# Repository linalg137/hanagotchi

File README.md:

# HANAGOTCHI

A small "tamagotchi", shaped like a flower. It has three interactive buttons and an OLED screen, and can play many different files-- coded in micropython. This isn't a generic "pet" tamagotchi-- you're guarding a dangerous invisible criminal-- try not to let them get out!!  

## ***Inspiration***
As a constant fiction writer, I've always wanted to create my own special dialogue-based game. This gave me the perfect chance to do so, while including extrenally aeshtetic pleasures as well.

## ***Full Instructions~***

**getting the pcb**
1. go to https://jlcpcb.com/. click "get instant quote".
2. download the gerber zip file from the pcb folder and upload it.
3. you can change the color of the PCB if you'd like, but keep all the other settings the same.
4. order your PCB by following the steps on the website.

**getting the parts**
1. To find all the suitable parts needed for this pcb, open the BOM file. This lists all the necessary parts needed for the PCB-- you'll see several links leading to product pages.

**printing the case**
1. download the STL files, or go open this onshape link: [https://cad.onshape.com/documents/30ca1b2b31257d2650154877/w/6a6ce5b2935f39e9888c6e90/e/9cf32ad964649424d66e1c2f?renderMode=0&uiState=6a1fb2345d12723005a9a689](https://cad.onshape.com/documents/cbb68b9589daf277c9578781/w/eef88f9737002ddb59d7612d/e/e6992a34dc4435c059d9da9e?renderMode=0&uiState=6a20adc240c23c91ee920c5a).
2. follow the directions on your own 3D printer's manufacturer's website/app to upload the STL files in and print them. support for the prints are not neeeded, as long as you have the models sitting on the correct side.

**soldering and putting everything together**
1. solder the pieces together in their designated spots. You can use the .step file to see how it should look like in the end (the battery cell is optional). 
2. After you're done soldering it, plug the ESP32 into your device using a USB-C.
3. Import micropython onto your ESP32 by uploading the ESP32_GENERIC_C3-20260406-v1.28.0.bin into the adafruit webserial bootloader (https://adafruit.github.io/Adafruit_WebSerial_ESPTool/)(to start this, click the "connect" button on the upper right corner. no offset is needed.).
4. upload the programs into the ESP32 using your coding development environment (ex; Thonny.) whenever you plug in the device, it should immeadiately start playing the intro (main) file!!

## ***GALLERY***
<details>
  <summary>3D model, PCB design, schematic, etc</summary>

</details>

## ***Credits~***
This project used:
- [KiCAD](https://www.kicad.org/) (for PCB design)
- [Onshape](https://www.onshape.com/en/platform) (for case design)
- [@TaniWanKenobi's Tamagotchi Guided Tutorial](https://fallout.hackclub.com/docs/guided-projects/tamagotchi) (for the base schematic layout)

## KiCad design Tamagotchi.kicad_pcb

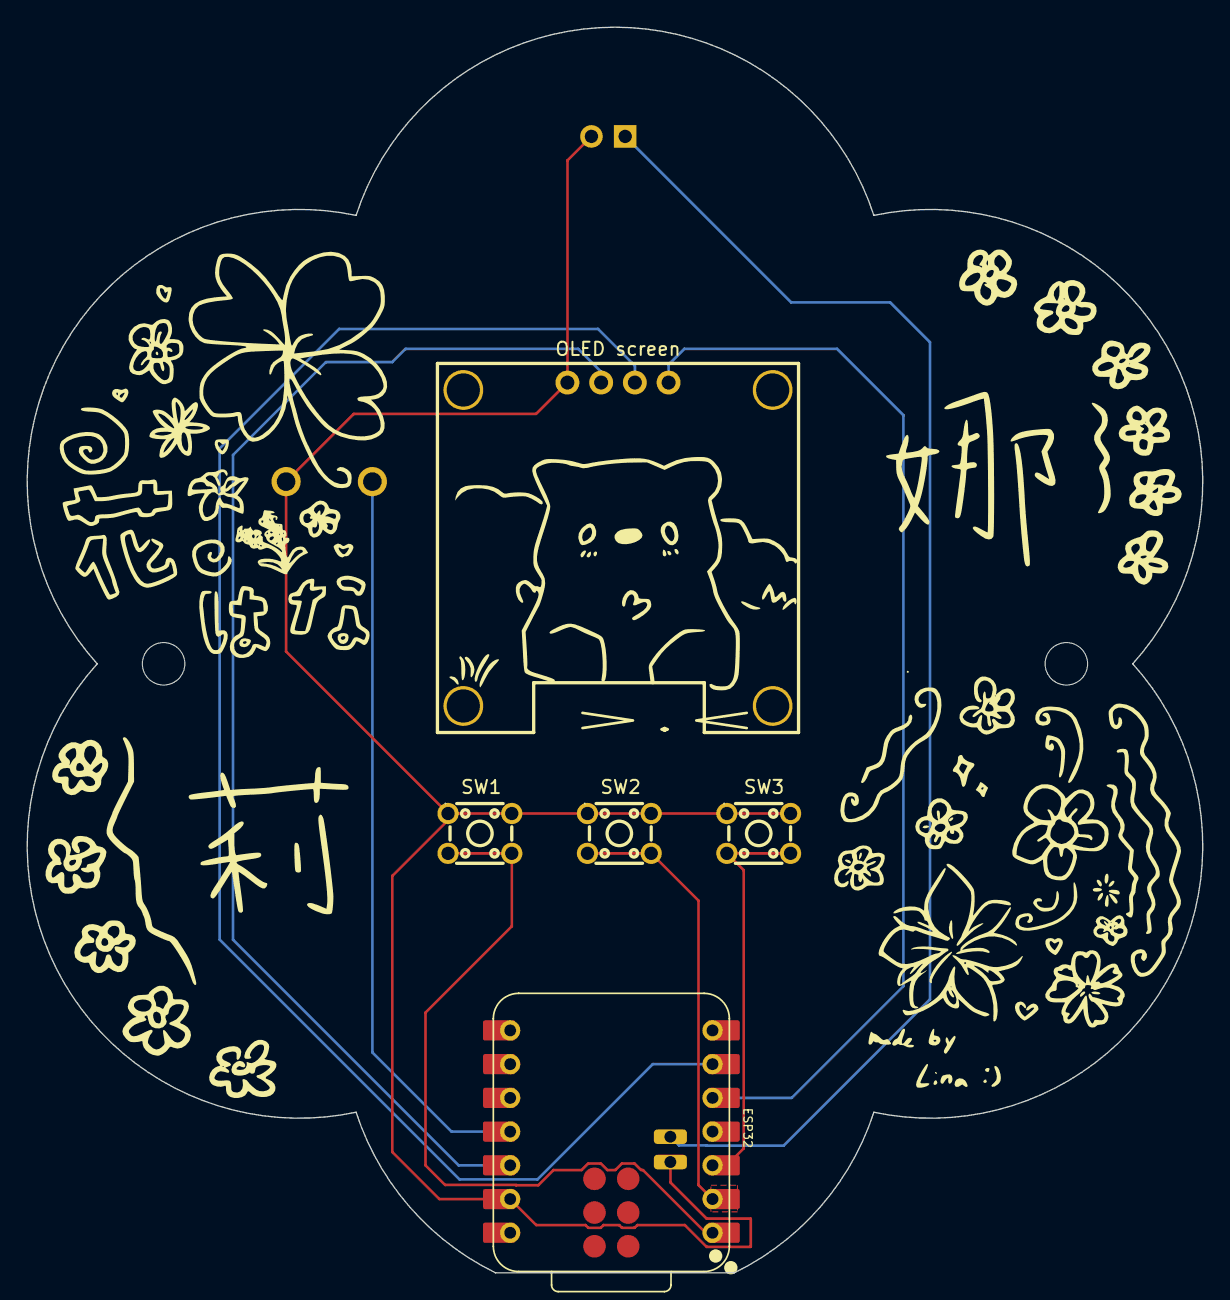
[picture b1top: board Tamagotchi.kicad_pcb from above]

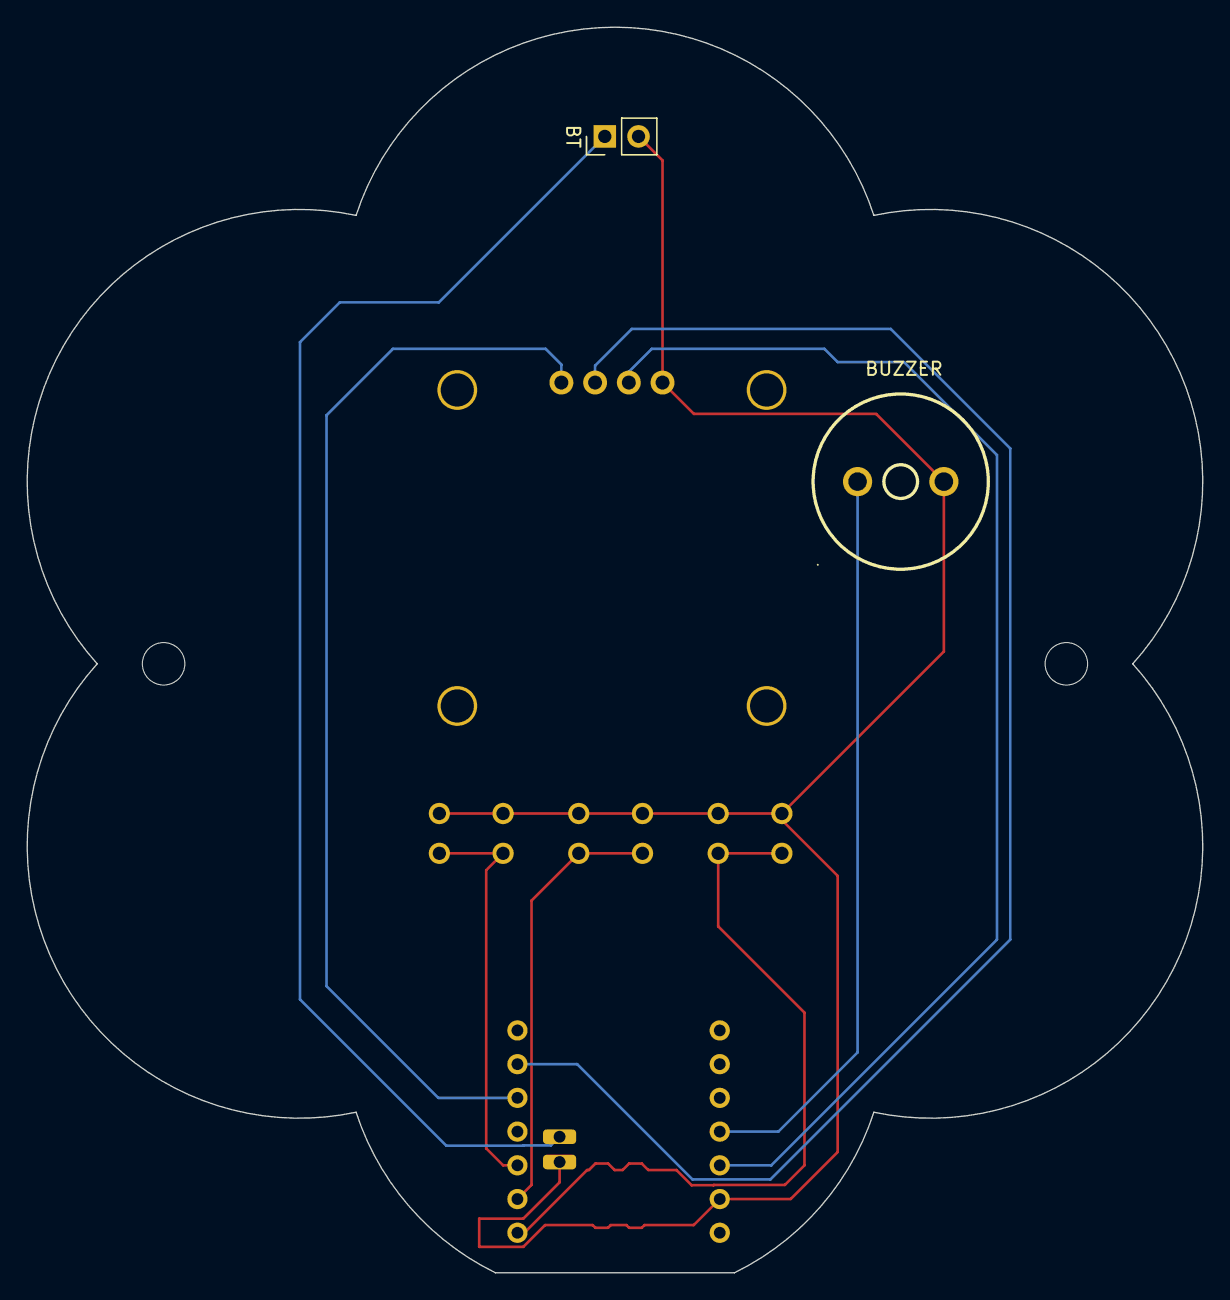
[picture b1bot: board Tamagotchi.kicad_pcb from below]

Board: 2 copper layers, 88.5 x 93.8 mm, 7 parts (2 on the bottom side), 9 nets.

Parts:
BT: Battery_Cell; PinHeader_1x02_P2.54mm_Vertical
BUZZER: 1207-P6.5MM; BUZ-TH_BD12.5-P6.50-D1.4
ESP32: XIAO-ESP32-C3-SMD; XIAO-ESP32-C3-DIP-SMD
OLED screen: HS96L03W2C03; OLED-TH_L27.8-W27.2-P2.54_C9900033791
SW1, SW2, SW3: SW_Push; SW-TH_4P-L4.5-W4.5-P3.00-LS4.8

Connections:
+3.3V: ESP32.12 (3V3), OLED screen.2 (VCC)
+BATT: BT.1 (+), ESP32.32 (BAT)
GND: BT.2 (-), BUZZER.2 (-), ESP32.13 (GND), ESP32.33 (GND), OLED screen.1 (GND), SW1.1, SW2.1, SW3.1
unnamed: BUZZER.1 (+), ESP32.11 (GPIO10_D10_MOSI)
unnamed: ESP32.6 (GPIO7_D5_SCL), OLED screen.3 (SCL)
unnamed: ESP32.5 (GPIO6_D4_SDA), OLED screen.4 (SDA)
unnamed: ESP32.1 (GPIO2_A0_D0), SW1.2
unnamed: ESP32.2 (GPIO3_A1_D1), SW2.2
unnamed: ESP32.3 (GPIO4_A2_D2), SW3.2

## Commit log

2026-05-27 README.md
2026-05-27 Add files via upload
    Library used to input XIAO-ESP32-C3-DIP-SMD onto kicad
2026-06-03 Create e
2026-06-03 Create ee
2026-06-03 Create CAD
